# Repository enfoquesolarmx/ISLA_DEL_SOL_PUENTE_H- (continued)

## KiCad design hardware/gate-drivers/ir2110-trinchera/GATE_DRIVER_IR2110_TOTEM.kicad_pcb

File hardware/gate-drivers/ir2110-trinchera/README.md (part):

# Módulo gate driver de medio puente H con IR2110 + tótem TIP41C/TIP42C — modo trinchera

**Proyecto:** Puente H — prototipo SPWM "Isla del Sol" (inversor 48 V → 127 V / 60 Hz, 1000 W; modo cargador 1 kVA)
**Módulo:** gate driver de **medio puente H** (una rama: MOSFET alto + MOSFET bajo), legacy / trinchera, con tótem por canal
**Intercambiable con:** IRS2186, UCC21520DW y TLP250 de trinchera (misma interfaz J2/J5, mismo firmware)
**Versión de placa:** V.0.1.NOV.26.J.G
**Estado:** diseño terminado; DRC con 0 errores y 0 elementos sin conectar; esquemático por bloques con guía de trinchera (2026-11-12). Pendiente: fabricación y validación en banco
**Fecha:** 2026-11-04 (esquemático por bloques: 2026-11-12)
**Documentos relacionados:** [`docs/identificacion_dt_pin9.md`](../../../docs/identificacion_dt_pin9.md), [`docs/sensado_corriente.md`](../../../docs/sensado_corriente.md), [módulo TLP250](../tlp250-trinchera/README.md), [módulo IRS2186](../irs2186/README.md)

| Cara de componentes | Cara de soldadura |
| --- | --- |
|  |  |

*Izquierda: arriba, la bornera J2 de entrada con R1 y R2 (10 kΩ, pull-down de HIN y LIN); en medio, el **IR2110 en DIP-14** con sus capacitores X7R; abajo, los **cuatro TO-220 del tótem** (TIP41C o D44H11 como NPN, TIP42C o D45H11 como PNP) y el header J5 hacia el puente H (H · VS1 · · · GK · L · G · 15V · llave · NC). La leyenda **"USAR SILICÓN RTV NEUTRO ENTRE TIPs"** recuerda fijar los transistores a la tarjeta con silicón de curado neutro. Derecha: la leyenda **"ATENCIÓN: DT = 1 µs — VALIDAR MOSFET Y SW"**, el regulador **78L05** (SOT-89) que da los 5 V de VDD, la red de bootstrap (2.2 Ω 1 W + ES1D), los dos **zener de 18 V** (Z1: VB1–VS1 y Z2: 15V–GND_K) y la **X** de la llave en la posición 8 de J5.*

*Esquemático por bloques (KiCad 9, hoja A3), pensado para quien arma y repara: **A** entrada J2 · **B** lógica de 5 V con 78L05 · **C** IR2110 · **D** 15 V del lado bajo · **E** bootstrap · **F** tótem alto · **G** tótem bajo · **H** salida J5 · **I** guía rápida de trinchera (ensamble y prueba sin MOSFET). Cada bloque dice qué medir y qué pasa si una pieza va al revés.*

## 0. Guía rápida de trinchera

**Antes de soldar:**

| Pieza | Cuidado | Si se hace mal |
| --- | --- | --- |
| U1 IR2110 | En **zócalo DIP-14**, muesca hacia el pin 1 | Se cambia sin cautín; al revés se quema al conectar |
| J5 | **Quitar el pin 8** del header (llave) | El módulo podría entrar al revés en el puente H |
| Z1 | Banda (cátodo) hacia **VB1** | Pone en corto el bootstrap: el MOSFET alto nunca enciende |
| Z2 | Banda (cátodo) hacia **15 V** | Se calienta y jala los 15 V |
| Q1–Q4 | NPN (TIP41C / D44H11G) arriba, PNP (TIP42C / D45H11G) abajo; acostados, aletas sin tocarse | NPN y PNP cruzados: la salida no sigue a la entrada |
| TIPs | Silicón RTV **neutro** entre los cuerpos y el PCB | El silicón acético corroe las patas |

**Prueba sin MOSFET** (15 V en J5-7; J5-6 y J5-4 a la tierra de la fuente; **J5-2 (VS1) unido a J5-4** para que cargue el bootstrap; J2 a la tarjeta de control o a 5 V):

| Medir | Entre | Debe dar |
| --- | --- | --- |
| VDD | Pin 9 y pin 13 del IR2110 | 5.0 V ± 0.25 V |
| VCC | Pin 3 y pin 2 | 15 V |
| SD | Pin 11 a GND | 0 V |
| Salidas con J2 suelto | HA_OUT (J5-1) y LA_OUT (J5-5) | 0 V |
| L = 5 V | LA_OUT a GND_K | ≈ 14 V (15 V menos el V_BE del tótem) |
| H = 5 V (después de un pulso de L, para cargar el bootstrap) | HA_OUT a VS1 | ≈ 13 V |
| Tiempo muerto | Lo que reporta el MCU | **1 µs** (P9 abierto) |

> Valores verificados contra `GATE_DRIVER_IR2110_TOTEM.kicad_pcb` (2026-11-04). Lo marcado *(verificar)* depende de la hoja de datos.

---
## 1. Qué maneja este módulo

Cada módulo maneja **una rama** del puente H: el **MOSFET del lado alto** (HO, referido a VS, alimentado por bootstrap) y el **MOSFET del lado bajo** (LO, referido a COM / GND_K).

```
            +48 V
              │
     HA ──► [MOSFET alto]          [MOSFET alto] ◄── HB
              │                         │
              ├── VS1 ──► transformador ◄── VS2 ──┤
              │                         │
     LA ──► [MOSFET bajo]          [MOSFET bajo] ◄── LB
              │                         │
             GND ───────────────────── GND
         └── módulo rama A ──┘    └── módulo rama B ──┘
```

- **El puente completo usa dos módulos iguales:** rama A (VS1) y rama B (VS2). En la rama B, "H" y "L" de J2 manejan HB y LB, y el pin "VS1" de J5 va a VS2.
- **Inversor (modulación híbrida):** rama A a **24 kHz**, rama B a **60 Hz**. **Cargador (unipolar):** las dos ramas a **24 kHz**.
- **Alcance: de 1 a 5 MOSFET por posición** (sección 6).

### 1.1 Por qué existe: modo trinchera

Igual que el módulo TLP250, este módulo existe para **cuando los drivers modernos no llegan**. El IR2110 (International Rectifier, hoy Infineon) es el driver de medio puente **más fácil de conseguir o rescatar**: está en variadores, soldadoras inverter y UPS viejos, y en casi cualquier tienda de electrónica. Viene en **DIP-14**: se monta en zócalo y se cambia sin cautín. Todo el módulo se arma con partes de tienda local.

| | TLP250 + tótem | **IR2110 + tótem (este)** |
| --- | --- | --- |
| Driver | Optoacoplador DIP-8, uno por canal | DIP-14, un chip para los dos canales |
| Aislamiento de la entrada | Sí (óptico) | Parcial: **VSS y COM separados**, hasta ±5 V |
| Diferencia de retardo entre canales | Hasta **400 ns** | **10–20 ns** |
| Margen dentro de 1 µs | ~150–250 ns con 2 IRF100P219 | **Mucho mayor** |
| Corriente propia | ~2 A | 2 A |
| MOSFET por posición | 1–2 IRF100P219 | **1–5** (por ejemplo 5 × IRF540N) |

---

## 2. Interfaz

### 2.1 J2 — entrada, hacia la tarjeta de control ("J1" de la interfaz)

Conector **Phoenix Contact SPT 1,5/5-H-3,5** (5 posiciones, paso 3.5 mm, de resorte), igual que el módulo IRS2186.

| Terminal | Señal | En este módulo |
| --- | --- | --- |
| 1 | H | HIN del IR2110 (pin 10), 10 kΩ a GND |
| 2 | GND | Tierra lógica = VSS (trenzar con H) |
| 3 | L | LIN del IR2110 (pin 12), 10 kΩ a GND |
| 4 | GND | Tierra lógica = VSS (trenzar con L) |
| **5** | **P9 — ID DT** | **Abierto, sin pista** → el MCU usa **1 µs** |

### 2.2 J5 — salida, hacia la tarjeta del puente H (header de 9 posiciones, 2.54 mm)

| Pin | Señal | Nota |
| --- | --- | --- |
| 1 | H (HA_OUT) | Emisores del tótem H |
| 2 | VS1 | Referencia del canal H |
| 3 | — | Libre (separación del nodo conmutado) |
| 4 | GK (GND_K) | Referencia Kelvin del canal L = **COM** |
| 5 | L (LA_OUT) | Emisores del tótem L |
| 6 | G (GND) | **Tierra lógica (VSS)**: retorno del 78L05 hacia la tarjeta del puente H |
| 7 | 15 V | Alimentación |
| 8 | **X** | **Llave mecánica:** sin pad; **quitar el pin 8 del header** |
| 9 | NC | Reservado |

### 2.3 Tierras: VSS y COM separados

El IR2110 tiene **dos tierras**: **VSS** (lógica) y **COM** (retorno del lado bajo), con hasta **±5 V** de diferencia permitida.

| Zona | Referencia | Componentes |
| --- | --- | --- |
| Lógica | **GND (VSS)** | J2, R1, R2, VSS (13), SD (11), 78L05, capacitor de entrada y de salida del 78L05, **J5-6** |
| Canal L (potencia) | **GND_K (COM)** | COM (2), colector de Q4 (PNP), C2, C4, C6, C8, Z2 |
| Canal H (HV, flota con VS1) | **VS1** | VS (5), Q2 colector, C3, C5, C9, Z1 |

- **J5-6 a GND lógico** (a diferencia del TLP250, que deja J5-6 sin conectar): el 78L05 toma sus 15 V de J5-7, así que su corriente regresa por el camino corto J5-6. Además, VSS queda bien referido respecto a COM.
- **COM va a GND_K (J5-4):** la corriente de compuerta del canal bajo regresa por GND_K y **no pasa por la tierra lógica**. Es la ventaja del IR2110 sobre el IRS2186.
- GND y GND_K se unen en **un solo punto en la tarjeta del puente H**, nunca dentro del módulo.
- **Lazo de tierra:** igual que con el IRS2186, el GND del cable J2 es un camino más hacia la tarjeta de control. Se controla con **par trenzado H/GND y L/GND** y la unión única de tierras.
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
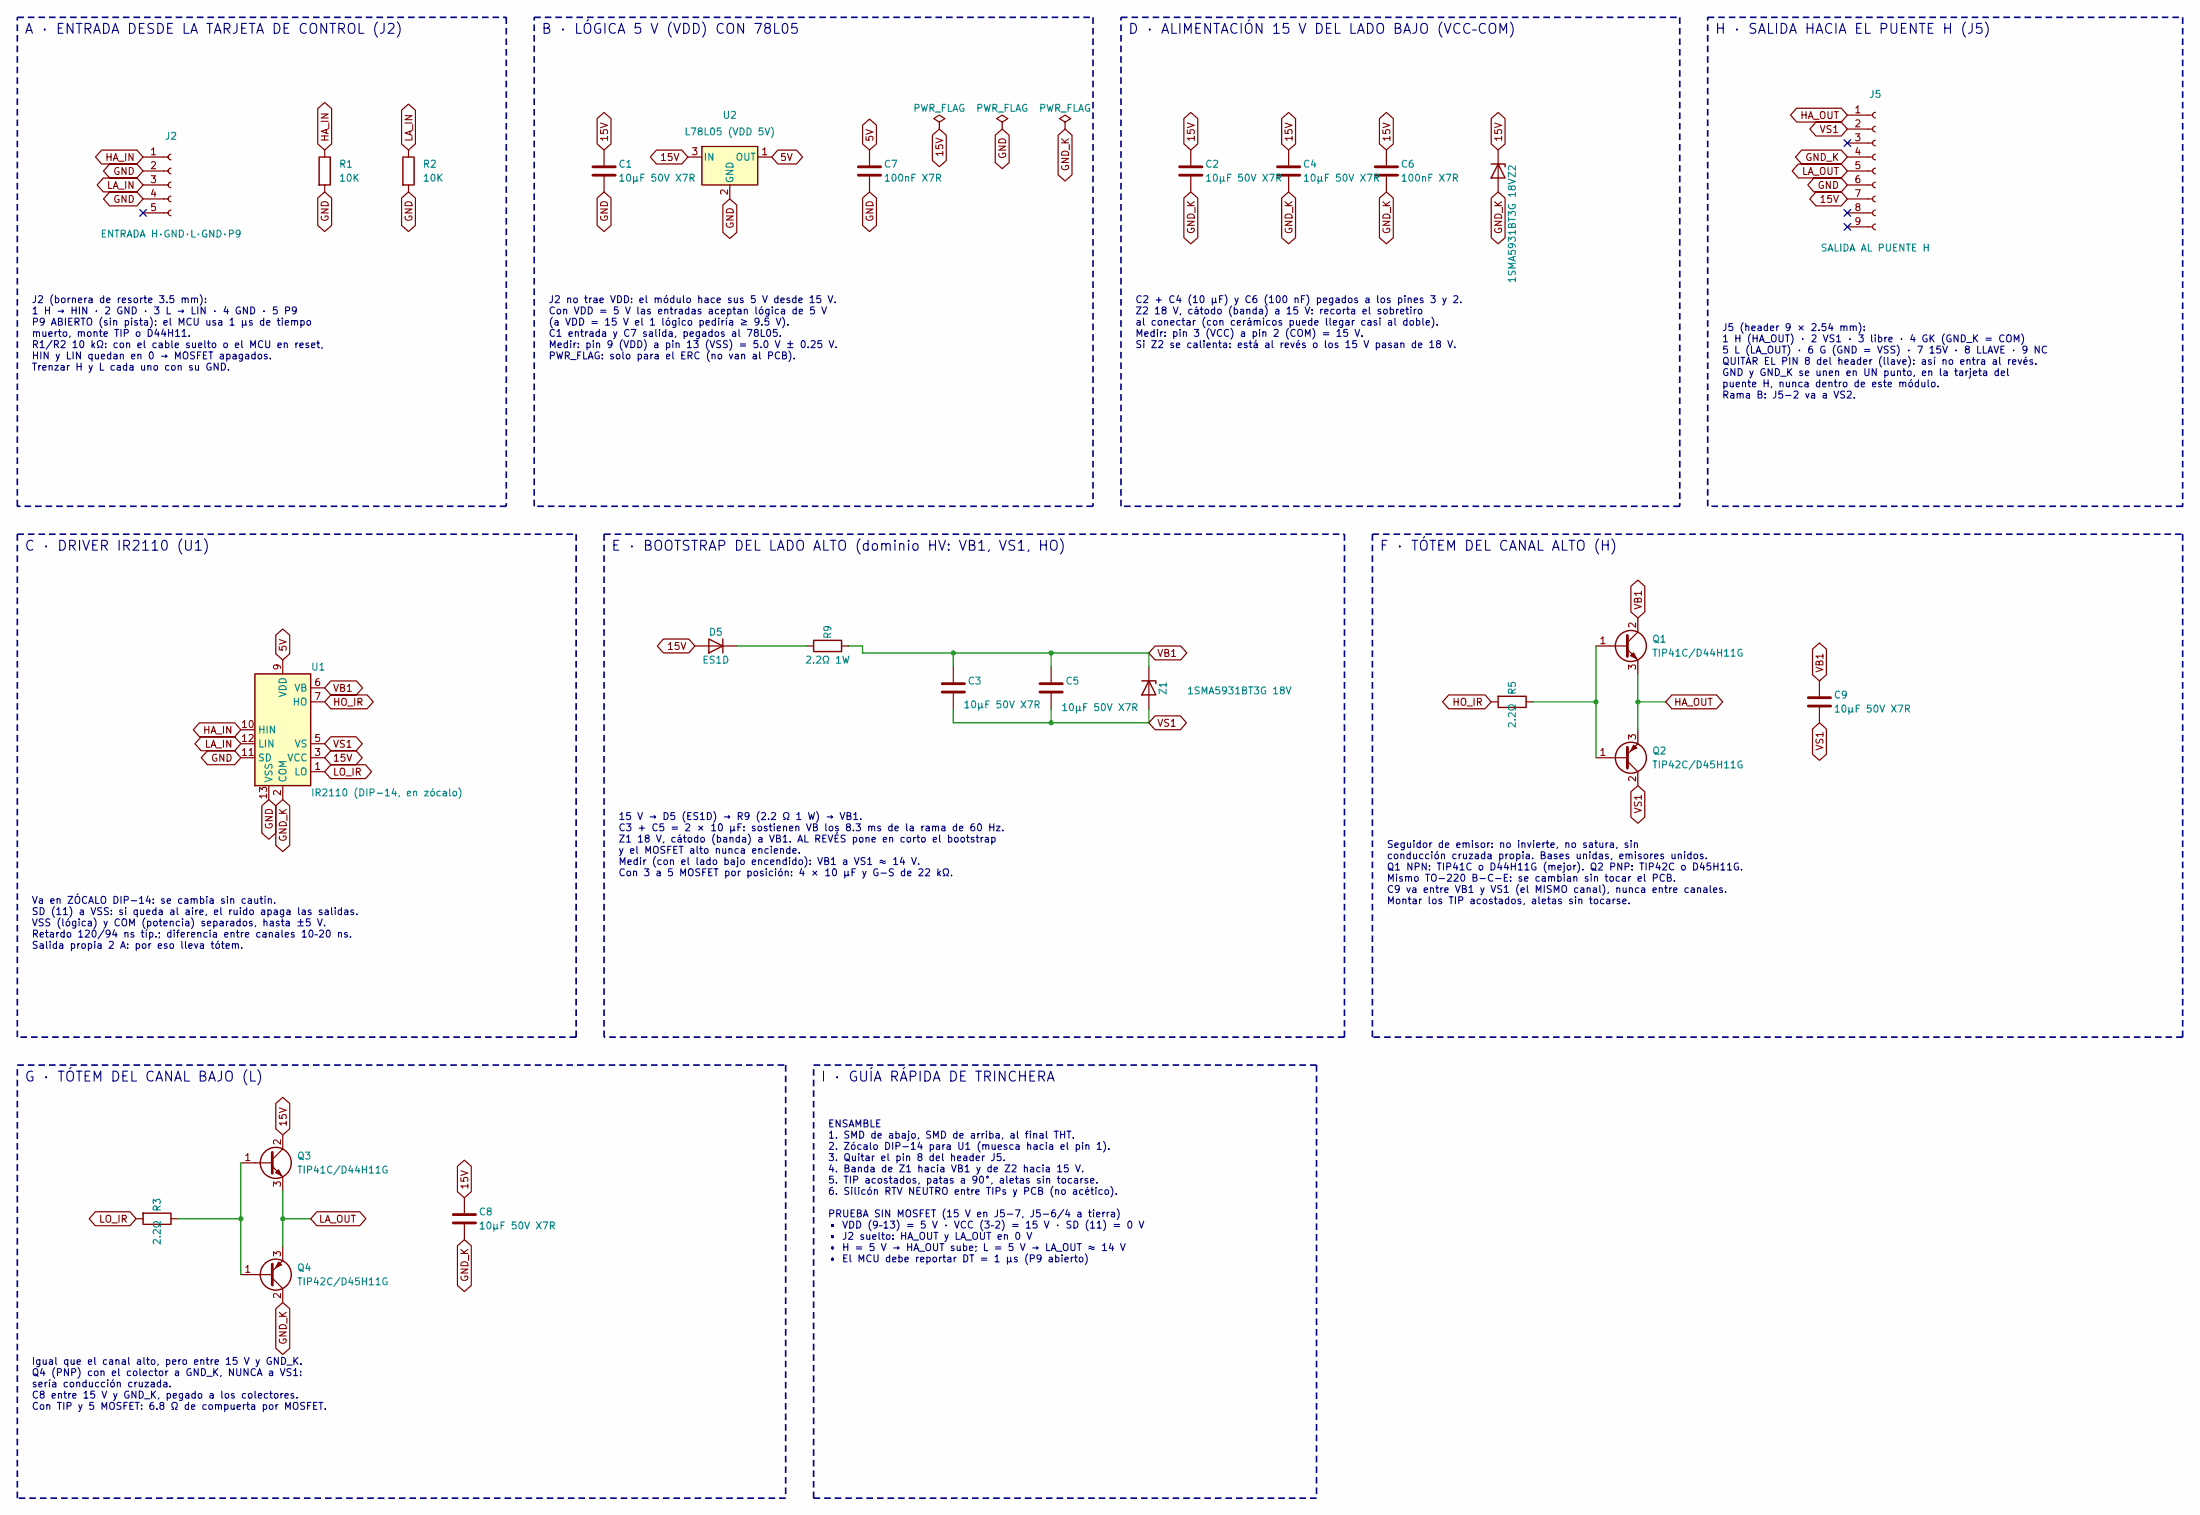
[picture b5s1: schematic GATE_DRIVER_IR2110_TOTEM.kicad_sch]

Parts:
C1, C2, C3, C4, C5, C8, C9: 10µF 50V X7R; C_1210_3225Metric_Pad1.33x2.70mm_HandSolder
C6, C7: 100nF X7R; C_1206_3216Metric
D5: ES1D; D_SMA
J2: ENTRADA H·GND·L·GND·P9; PhoenixContact_SPT_1.5_5-H-3.5_1x05_P3.5mm_Horizontal
J5: SALIDA AL PUENTE H; PinHeader_1x09_P2.54mm_Vertical
Q1, Q3: TIP41C/D44H11G; TO-220-3_Vertical
Q2, Q4: TIP42C/D45H11G; TO-220-3_Vertical
R1, R2: 10K; R_1206_3216Metric_Pad1.30x1.75mm_HandSolder
R3, R5: 2.2Ω; R_1206_3216Metric_Pad1.30x1.75mm_HandSolder
R9: 2.2Ω 1W; R_1210_3225Metric
U1: IR2110 (DIP-14, en zócalo); DIP-14_W7.62mm
U2: L78L05 (VDD 5V); SOT-89-3
Z1, Z2: 1SMA5931BT3G 18V; D_SMA

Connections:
5V: C7.1, U1.9 (VDD), U2.1 (OUT)
15V: C1.1, C2.1, C4.1, C6.1, C8.1, D5.2 (A), J5.7, Q3.2 (C), U1.3 (VCC), U2.3 (IN), Z2.1 (K)
GND: C1.2, C7.2, J2.2, J2.4, J5.6, R1.2, R2.2, U1.11 (SD), U1.13 (VSS), U2.2 (GND)
GND_K: C2.2, C4.2, C6.2, C8.2, J5.4, Q4.2 (C), U1.2 (COM), Z2.2 (A)
HA_IN: J2.1, R1.1, U1.10 (HIN)
HA_OUT: J5.1, Q1.3 (E), Q2.3 (E)
HO_IR: R5.2, U1.7 (HO)
LA_IN: J2.3, R2.1, U1.12 (LIN)
LA_OUT: J5.5, Q3.3 (E), Q4.3 (E)
LO_IR: R3.2, U1.1 (LO)
unnamed: D5.1 (K), R9.2
unnamed: Q1.1 (B), Q2.1 (B), R5.1
unnamed: Q3.1 (B), Q4.1 (B), R3.1
VB1: C3.1, C5.1, C9.1, Q1.2 (C), R9.1, U1.6 (VB), Z1.1 (K)
VS1: C3.2, C5.2, C9.2, J5.2, Q2.2 (C), U1.5 (VS), Z1.2 (A)

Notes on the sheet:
H · SALIDA HACIA EL PUENTE H (J5)
ENSAMBLE 1. SMD de abajo, SMD de arriba, al final THT. 2. Zócalo DIP-14 para U1 (muesca hacia el pin 1). 3. Quitar el pin 8 del header J5. 4. Banda de Z1 hacia VB1 y de Z2 hacia 15 V. 5. TIP acostados, patas a 90°, aletas sin tocarse. 6. Silicón RTV NEUTRO entre TIPs y PCB (no acético). PRUEBA SIN 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
I · GUÍA RÁPIDA DE TRINCHERA
C2 + C4 (10 µF) y C6 (100 nF) pegados a los pines 3 y 2. Z2 18 V, cátodo (banda) a 15 V: recorta el sobretiro al conectar (con cerámicos puede llegar casi al doble). Medir: pin 3 (VCC) a pin 2 (COM) = 15 V. Si Z2 se calienta: está al revés o los 15 V pasan de 18 V.
E · BOOTSTRAP DEL LADO ALTO (dominio HV: VB1, VS1, HO)
A · ENTRADA DESDE LA TARJETA DE CONTROL (J2)
F · TÓTEM DEL CANAL ALTO (H)
Seguidor de emisor: no invierte, no satura, sin conducción cruzada propia. Bases unidas, emisores unidos. Q1 NPN: TIP41C o D44H11G (mejor). Q2 PNP: TIP42C o D45H11G. Mismo TO-220 B-C-E: se cambian sin tocar el PCB. C9 va entre VB1 y VS1 (el MISMO canal), nunca entre canales. Montar los TIP acostado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
B · LÓGICA 5 V (VDD) CON 78L05
Igual que el canal alto, pero entre 15 V y GND_K. Q4 (PNP) con el colector a GND_K, NUNCA a VS1: sería conducción cruzada. C8 entre 15 V y GND_K, pegado a los colectores. Con TIP y 5 MOSFET: 6.8 Ω de compuerta por MOSFET.
D · ALIMENTACIÓN 15 V DEL LADO BAJO (VCC–COM)
Va en ZÓCALO DIP-14: se cambia sin cautín. SD (11) a VSS: si queda al aire, el ruido apaga las salidas. VSS (lógica) y COM (potencia) separados, hasta ±5 V. Retardo 120/94 ns típ.; diferencia entre canales 10–20 ns. Salida propia 2 A: por eso lleva tótem.
G · TÓTEM DEL CANAL BAJO (L)
C · DRIVER IR2110 (U1)
15 V → D5 (ES1D) → R9 (2.2 Ω 1 W) → VB1. C3 + C5 = 2 × 10 µF: sostienen VB los 8.3 ms de la rama de 60 Hz. Z1 18 V, cátodo (banda) a VB1. AL REVÉS pone en corto el bootstrap y el MOSFET alto nunca enciende. Medir (con el lado bajo encendido): VB1 a VS1 ≈ 14 V. Con 3 a 5 MOSFET por posición: 4 × 10 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
J5 (header 9 × 2.54 mm): 1 H (HA_OUT) · 2 VS1 · 3 libre · 4 GK (GND_K = COM) 5 L (LA_OUT) · 6 G (GND = VSS) · 7 15V · 8 LLAVE · 9 NC QUITAR EL PIN 8 del header (llave): así no entra al revés. GND y GND_K se unen en UN punto, en la tarjeta del puente H, nunca dentro de este módulo. Rama B: J5-2 va a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
J2 (bornera de resorte 3.5 mm): 1 H → HIN · 2 GND · 3 L → LIN · 4 GND · 5 P9 P9 ABIERTO (sin pista): el MCU usa 1 µs de tiempo muerto, monte TIP o D44H11. R1/R2 10 kΩ: con el cable suelto o el MCU en reset, HIN y LIN quedan en 0 → MOSFET apagados. Trenzar H y L cada uno con su GND.
J2 no trae VDD: el módulo hace sus 5 V desde 15 V. Con VDD = 5 V las entradas aceptan lógica de 5 V (a VDD = 15 V el 1 lógico pediría ≥ 9.5 V). C1 entrada y C7 salida, pegados al 78L05. Medir: pin 9 (VDD) a pin 13 (VSS) = 5.0 V ± 0.25 V. PWR_FLAG: solo para el ERC (no van al PCB).

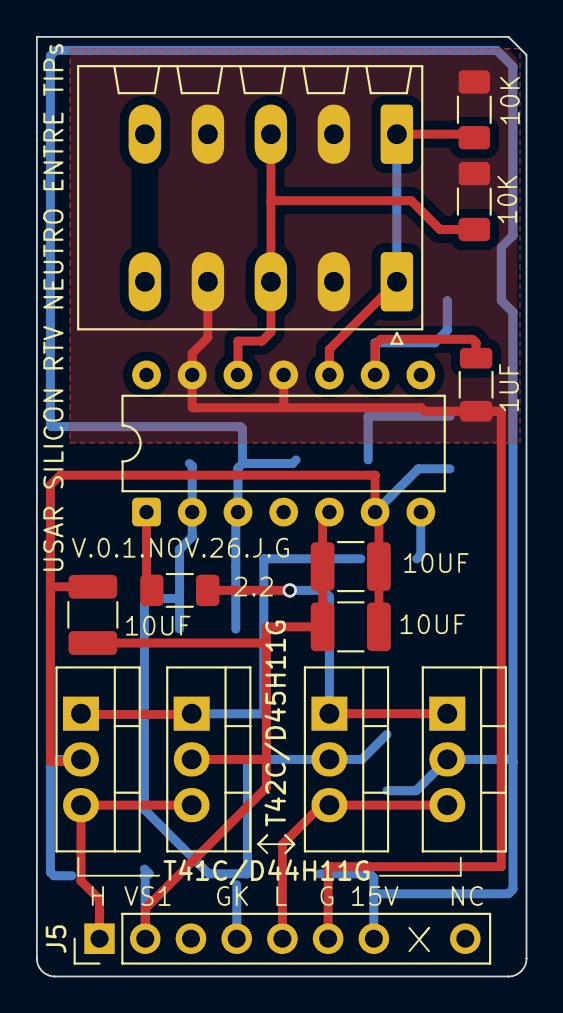
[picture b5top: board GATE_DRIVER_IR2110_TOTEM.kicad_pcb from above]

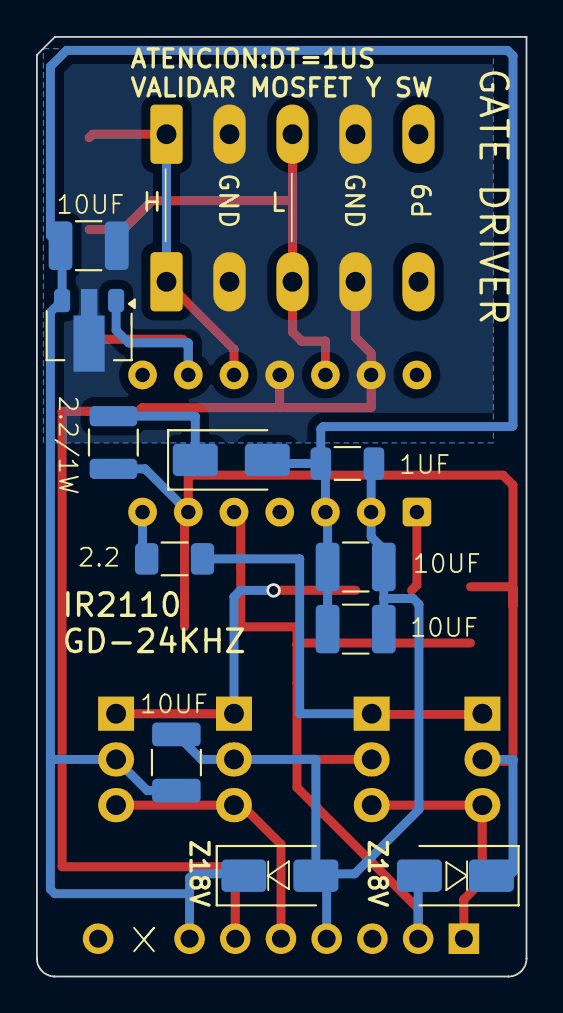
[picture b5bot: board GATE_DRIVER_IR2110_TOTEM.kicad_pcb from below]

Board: 2 copper layers, 27.2 x 52.2 mm, 25 parts (11 on the bottom side), 15 nets.

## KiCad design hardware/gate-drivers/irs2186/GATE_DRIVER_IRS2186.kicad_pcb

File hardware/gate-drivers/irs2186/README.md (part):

# Módulo gate driver de medio puente H con IRS2186

**Proyecto:** Puente H — prototipo SPWM "Isla del Sol" (inversor 48 V → 127 V / 60 Hz, 1000 W; modo cargador 1 kVA)
**Módulo:** gate driver de **medio puente H** (una rama: MOSFET alto + MOSFET bajo) con bootstrap. Es el **módulo principal de producción**: bajo costo y 500 ns de tiempo muerto
**Intercambiable con:** UCC21520DW y TLP250 de trinchera (misma interfaz J1/J5, mismo firmware)
**Estado:** diseño terminado con P9 en J1; esquemático reordenado por bloques (2026-11-12). Pendiente: DRC final, fabricación y validación en banco
**Fecha:** 2026-11-03 (esquemático por bloques: 2026-11-12)
**Documentos relacionados:** [`docs/identificacion_dt_pin9.md`](../../../docs/identificacion_dt_pin9.md), [`docs/compensacion_adaptativa_tiempo_muerto.md`](../../../docs/compensacion_adaptativa_tiempo_muerto.md), [módulo TLP250](../tlp250-trinchera/README.md)

> Verificar los valores marcados con *(verificar)* contra el esquemático de KiCad antes de fabricar.

| Cara de componentes | Cara de soldadura |
| --- | --- |
|  |  |

*Esquemático por bloques (KiCad 9, hoja A4): **A** entrada J1 con R1/R2 y P9 · **B** alimentación de 15 V · **C** IRS2186 · **D** bootstrap · **E** salida J5 y NT1 · **F** reglas de firmware y compras. Cada bloque lleva su nota de diseño.*

*Izquierda: arriba, la bornera J1 de entrada (**P**9 · GND · L · GND · H); en medio, el IRS2186 (SOIC-8) con su desacoplo de 15 V (1 µF + 10 µF), la red de bootstrap (2.2 Ω 1 W + ES1D), el zener D6 de 18 V (1SMA5931BT3G), los capacitores de bootstrap (2 × 10 µF) y el electrolítico de respaldo de 15 V; abajo, el header J5 hacia el puente H (HO · VS1 · · · Gk · LO · G · 15V · llave). Derecha: la leyenda de seguridad **"ATENCIÓN: DT 500 ns MIN — VALIDAR MOSFET Y SW"**, la versión V.0.1.NOV.26.J.G y la **X** de la llave en la posición 8 de J5.*

---

## 1. Qué maneja este módulo

Cada módulo maneja **una rama** del puente H: el **MOSFET del lado alto** (HO, referido a VS, alimentado por bootstrap) y el **MOSFET del lado bajo** (LO, referido a COM).

```
            +48 V
              │
     HA ──► [MOSFET alto]          [MOSFET alto] ◄── HB
              │                         │
              ├── VS1 ──► transformador ◄── VS2 ──┤
              │                         │
     LA ──► [MOSFET bajo]          [MOSFET bajo] ◄── LB
              │                         │
             GND ───────────────────── GND
         └── módulo rama A ──┘    └── módulo rama B ──┘
```

- **El puente completo usa dos módulos iguales:** rama A (VS1) y rama B (VS2). En la rama B, "H" y "L" de J1 manejan HB y LB, y el pin "VS1" de J5 va a VS2.
- **Inversor (modulación híbrida):** rama A a **24 kHz**, rama B a **60 Hz**.
- **Cargador (unipolar):** las dos ramas a **24 kHz**.
- **Alcance:** **1 IRF100P219 por posición** (o hasta 2 IRF540N) con 500 ns. Para más carga de compuerta hace falta tótem rápido o el módulo UCC21520 (ver sección 6).

### Por qué el IRS2186

| Criterio | IRS2186 (este) | UCC21520DW | TLP250 + tótem |
| --- | --- | --- | --- |
| Costo y número de componentes | **El menor** ✓ | Medio | El mayor |
| Tiempo muerto | **500 ns** ✓ | 500 ns | 1 µs |
| Corriente de salida | 4 A / 4 A | 4 A / 6 A | ~2 A (más con tótem) |
| Aislamiento entrada / potencia | **No** (lógica referida a COM) | Sí | Sí |
| Reparación a mano | SOIC-8 | SOIC-16 ancho | DIP y TO-220 |

---

## 2. Interfaz

### 2.1 J1 — entrada, hacia la tarjeta de control (bornera de 5 terminales)

| Terminal | Señal | En este módulo |
| --- | --- | --- |
| 1 | H | HIN del IRS2186 (con 10 kΩ a GND) |
| 2 | GND | Tierra lógica = COM (trenzar con H) |
| 3 | L | LIN del IRS2186 (con 10 kΩ a GND) |
| 4 | GND | Tierra lógica = COM (trenzar con L) |
| **5** | **P9 — ID DT** | **Unido a GND** → el MCU usa **500 ns** |

- Serigrafía: "TRENZAR H Y L CON GND", etiquetas H / GND / L / GND / P9. Recomendado agregar **"OPERACION DT IRS2186=500NS"**.
- Las resistencias de 10 kΩ de HIN y LIN a GND mantienen los MOSFET apagados si la tarjeta de control no está conectada o el MCU está en reset.
- Si P9 queda con soldadura fría o cable suelto, el MCU lee 1 → **1 µs** (falla segura: funciona con más armónicos).

### 2.2 J5 — salida, hacia la tarjeta del puente H (header de 9 posiciones, 2.54 mm)

| Pin | Señal | Nota |
| --- | --- | --- |
| 1 | HO | Compuerta lado alto |
| 2 | VS1 | Fuente lado alto (nodo de conmutación) |
| 3 | — | Libre (separación del nodo conmutado) |
| 4 | GND_K | Retorno Kelvin del lado bajo |
| 5 | LO | Compuerta lado bajo |
| 6 | GND | Tierra de potencia |
| 7 | 15 V | Alimentación |
| 8 | — | **Llave mecánica:** sin pad; **quitar el pin 8 del header**; "X" en serigrafía |
| 9 | GND | Reservado (no se lee) |

### 2.3 Tierras: la entrada comparte la tierra de potencia

En el IRS2186 la lógica (HIN, LIN) va referida a **COM**, que también es el retorno del lado bajo. Por eso **el GND de J1 es la misma tierra de potencia**: el módulo no aísla la tarjeta de control.

Consecuencias y cuidados:

1. **Lazo de tierra:** el GND del cable J1 es un camino más entre la tarjeta de control y la potencia; con dos módulos (rama A y B) ya hay dos. Parte de la corriente de conmutación puede circular por esos cables.
2. **Rebote de tierra:** el di/dt del MOSFET bajo puede mover COM unos cientos de mV respecto al GND del MCU. El IRS2186 tiene umbrales de entrada de ~0.8 V / ~2.5 V *(verificar en la hoja de datos)*; con MCU a 5 V el margen es mayor.
3. **Medidas:**
   - **Par trenzado H/GND y L/GND, lo más corto posible.**
   - **Un solo punto de unión** entre tierra de control y tierra de potencia en la tarjeta del puente H (estrella), cerca de la fuente del MOSFET bajo o del shunt.
   - **Retorno de LO hacia GND_K** (Kelvin) y lógica hacia GND, unidos en un solo punto: la corriente de compuerta no debe pasar por la tierra de las entradas.
4. Si en banco aparecen disparos falsos o ruido en las entradas, los módulos **UCC21520** o **TLP250** lo eliminan por diseño (entrada aislada).

---

## 3. Circuito

### 3.1 IRS2186 (SOIC-8)

| Pin | Señal | Conexión |
| --- | --- | --- |
| 1 | HIN | J1-H, 10 kΩ a GND |
| 2 | LIN | J1-L, 10 kΩ a GND |
| 3 | COM | GND (tierra lógica y retorno del lado bajo) |
| 4 | LO | J5-5 |
| 5 | VCC | 15 V, con desacoplo a COM |
| 6 | VS | J5-2 (VS1) |
| 7 | HO | J5-1 |
| 8 | VB | VB1, nodo del bootstrap |

Verificar contra la hoja de datos de la variante comprada (IRS2186S, SOIC-8).

**Datos de la hoja de datos (Infineon IRS2186):** salida 4 A / 4 A; retardo de propagación ~170 ns típ., 250 ns máx.; diferencia entre canales ≤ 35 ns; VCC 10–20 V; offset VS hasta 600 V *(verificar)*.

### 3.2 Alimentación de 15 V (lado bajo)

- 15 V desde J5-7 a VCC, con desacoplo **10 µF + 1 µF X7R** pegados a los pines 5 y 3, más capacitor electrolítico de respaldo en la línea de 15 V *(verificar valores)*.
- **¿Por qué 15 V y no 12 V?** Más voltaje de compuerta (menor R_DS(on) y más margen de UVLO en el bootstrap de la rama de 60 Hz) dentro del rango de VCC del IRS2186 y del ±20 V de V_GS del MOSFET.

### 3.3 Bootstrap (lado alto)

```
15 V ── D5 (ES1D / ES1J) ── R9 2.2 Ω 1 W ──┬── VB1 (pin 8)
                                           ├── C2 + C9: 2 × 10 µF X7R 50 V 1206 ── VS1
                                           └── D6 zener 18 V (1SMA5931BT3G), cátodo a VB1 ── VS1
```

| Componente | Valor | Por qué |
| --- | --- | --- |
| R9 | 2.2 Ω, 1 W, **después del diodo** (entre el cátodo de D5 y VB1) | Limita el pico de recarga del bootstrap cuando VS cae a 0 V y, en esta posición, también la corriente de recuperación inversa de D5 cuando VS sube (IR Design Tip DT98-2; TI SLUA887A; patente US5969964, ya expirada). La resistencia en serie con el diodo cumple igual antes o después de él |
| D5 | ES1D (200 V) o **ES1J (600 V)** | Diodo **ultrarrápido** (no Schottky). ES1D limita el bus del módulo a ~120 V; con ES1J el límite lo ponen las separaciones del PCB (≤ 150 V) |
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
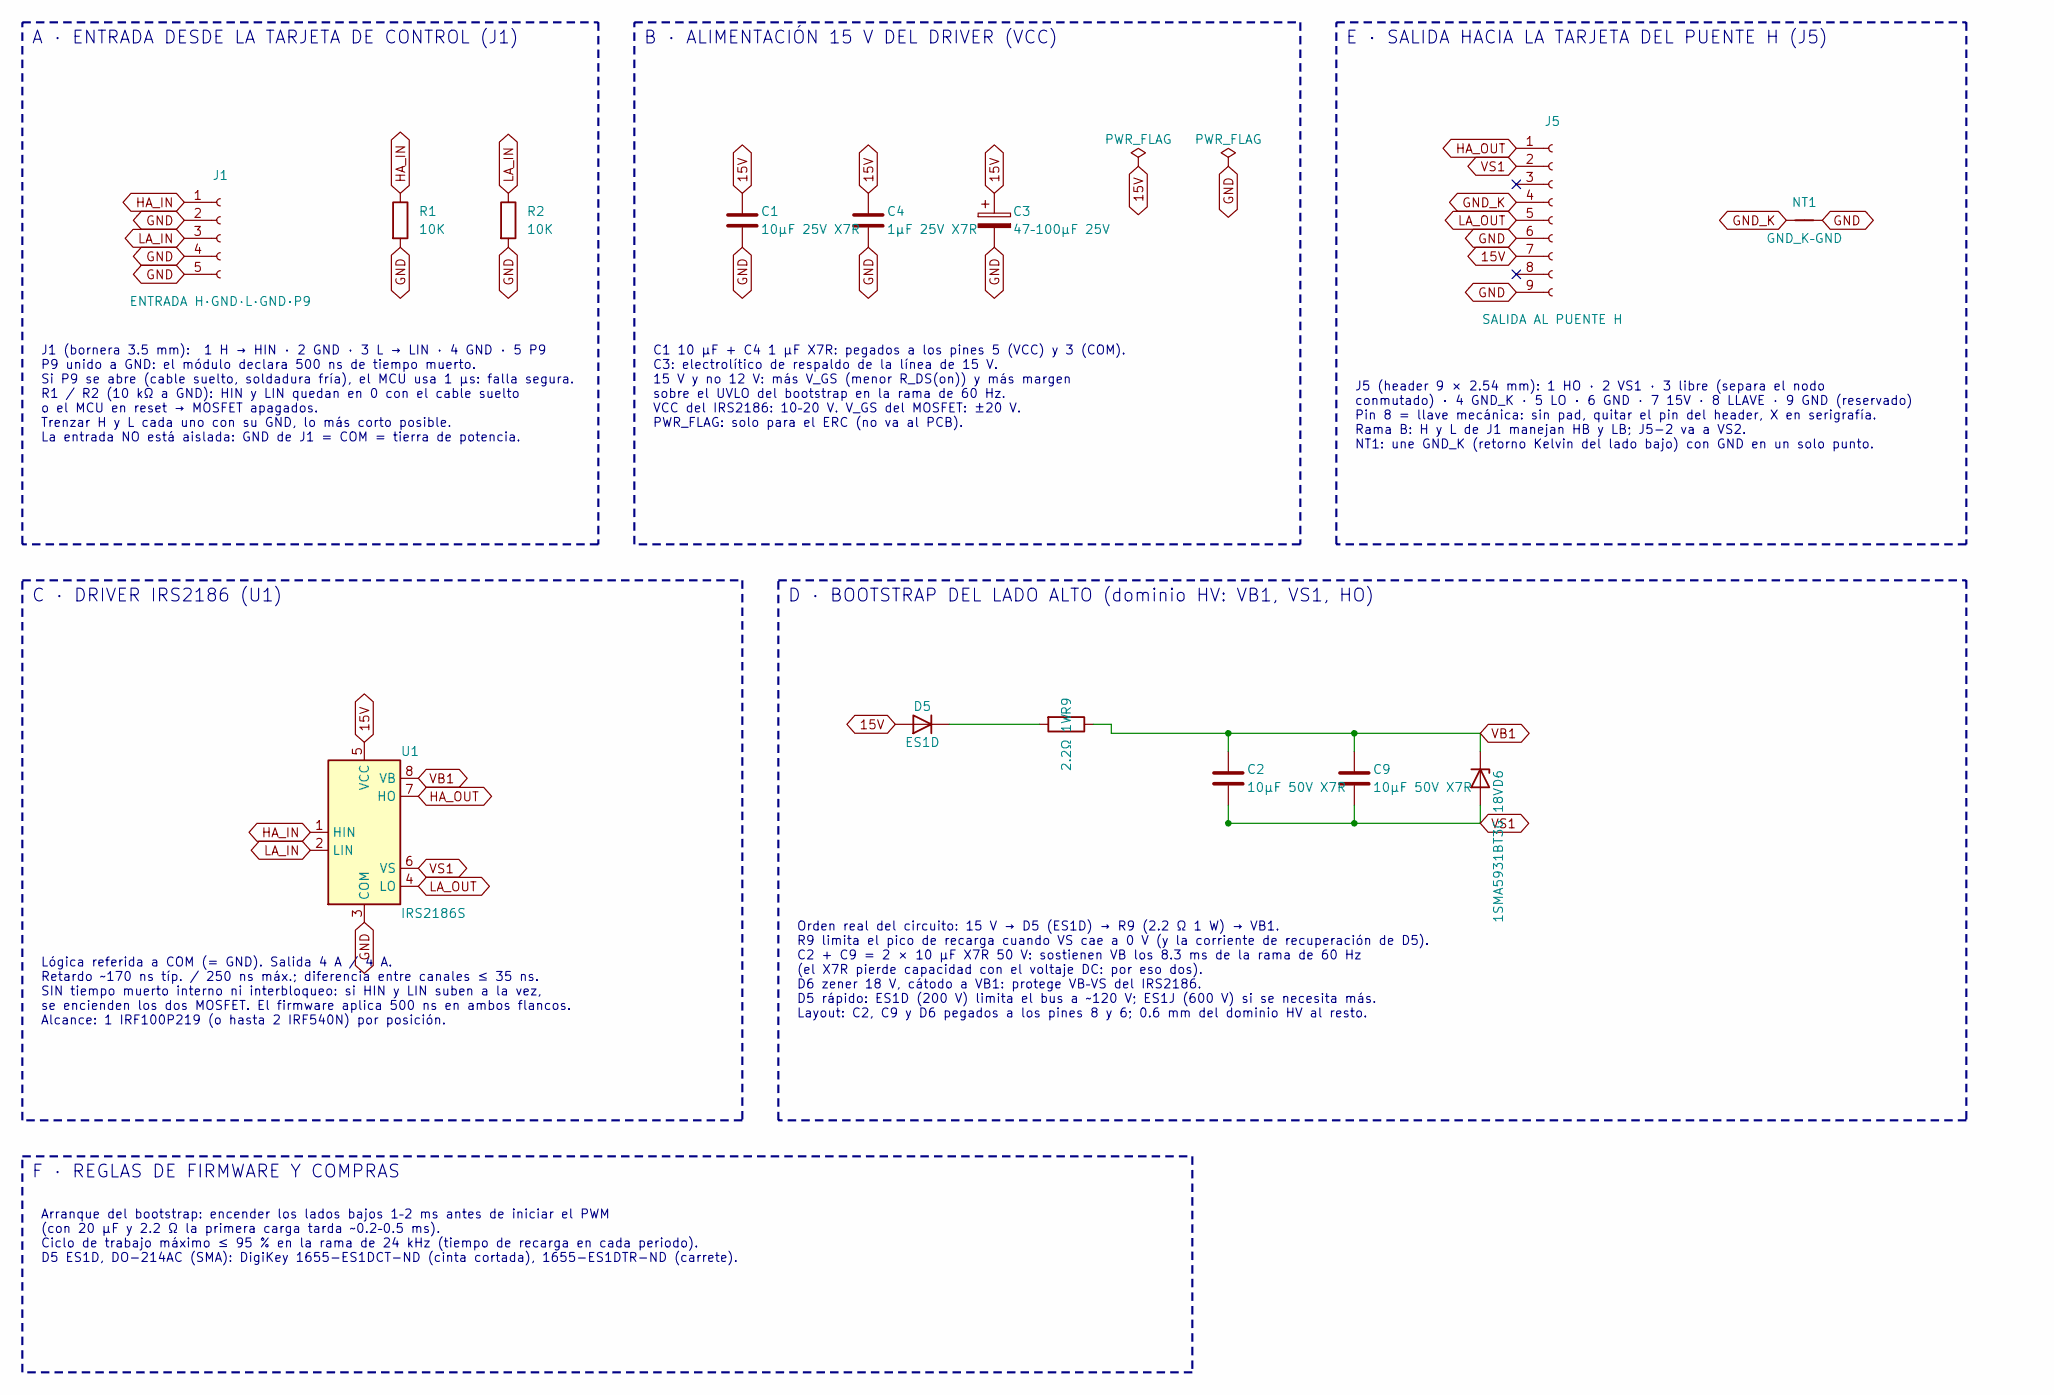
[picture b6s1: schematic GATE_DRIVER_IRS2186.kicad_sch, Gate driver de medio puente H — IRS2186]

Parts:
C1: 10µF 25V X7R; C_1206_3216Metric
C2, C9: 10µF 50V X7R; C_1206_3216Metric
C3: 47–100µF 25V; CP_Radial_D8.0mm_P3.50mm
C4: 1µF 25V X7R; C_1206_3216Metric
D5: ES1D; D_SMA
D6: 1SMA5931BT3G 18V; D_SMA
J1: ENTRADA H·GND·L·GND·P9; PhoenixContact_SPT_1.5_5-H-3.5_1x05_P3.5mm_Horizontal
J5: SALIDA AL PUENTE H; PinHeader_1x09_P2.54mm_Vertical
NT1: GND_K–GND; NetTie-2_SMD_Pad0.5mm
R1, R2: 10K; R_1206_3216Metric_Pad1.30x1.75mm_HandSolder
R9: 2.2Ω 1W; R_1210_3225Metric
U1: IRS2186S; SOIC-8_3.9x4.9mm_P1.27mm

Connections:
15V: C1.1, C3.1, C4.1, D5.2 (A), J5.7, U1.5 (VCC)
GND: C1.2, C3.2, C4.2, J1.2, J1.4, J1.5, J5.6, J5.9, NT1.2, R1.2, R2.2, U1.3 (COM)
GND_K: J5.4, NT1.1
HA_IN: J1.1, R1.1, U1.1 (HIN)
HA_OUT: J5.1, U1.7 (HO)
LA_IN: J1.3, R2.1, U1.2 (LIN)
LA_OUT: J5.5, U1.4 (LO)
unnamed: D5.1 (K), R9.2
VB1: C2.1, C9.1, D6.1 (K), R9.1, U1.8 (VB)
VS1: C2.2, C9.2, D6.2 (A), J5.2, U1.6 (VS)

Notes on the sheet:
A · ENTRADA DESDE LA TARJETA DE CONTROL (J1)
J1 (bornera 3.5 mm): 1 H → HIN · 2 GND · 3 L → LIN · 4 GND · 5 P9 P9 unido a GND: el módulo declara 500 ns de tiempo muerto. Si P9 se abre (cable suelto, soldadura fría), el MCU usa 1 µs: falla segura. R1 / R2 (10 kΩ a GND): HIN y LIN quedan en 0 con el cable suelto o el MCU en reset → MOSFET apaga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
B · ALIMENTACIÓN 15 V DEL DRIVER (VCC)
C1 10 µF + C4 1 µF X7R: pegados a los pines 5 (VCC) y 3 (COM). C3: electrolítico de respaldo de la línea de 15 V. 15 V y no 12 V: más V_GS (menor R_DS(on)) y más margen sobre el UVLO del bootstrap en la rama de 60 Hz. VCC del IRS2186: 10–20 V. V_GS del MOSFET: ±20 V. PWR_FLAG: solo para el ERC (no 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
E · SALIDA HACIA LA TARJETA DEL PUENTE H (J5)
J5 (header 9 × 2.54 mm): 1 HO · 2 VS1 · 3 libre (separa el nodo conmutado) · 4 GND_K · 5 LO · 6 GND · 7 15V · 8 LLAVE · 9 GND (reservado) Pin 8 = llave mecánica: sin pad, quitar el pin del header, X en serigrafía. Rama B: H y L de J1 manejan HB y LB; J5-2 va a VS2. NT1: une GND_K (retorno Kelvin de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
C · DRIVER IRS2186 (U1)
Lógica referida a COM (= GND). Salida 4 A / 4 A. Retardo ~170 ns típ. / 250 ns máx.; diferencia entre canales ≤ 35 ns. SIN tiempo muerto interno ni interbloqueo: si HIN y LIN suben a la vez, se encienden los dos MOSFET. El firmware aplica 500 ns en ambos flancos. Alcance: 1 IRF100P219 (o hasta 2 IR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
D · BOOTSTRAP DEL LADO ALTO (dominio HV: VB1, VS1, HO)
Orden real del circuito: 15 V → D5 (ES1D) → R9 (2.2 Ω 1 W) → VB1. R9 limita el pico de recarga cuando VS cae a 0 V (y la corriente de recuperación de D5). C2 + C9 = 2 × 10 µF X7R 50 V: sostienen VB los 8.3 ms de la rama de 60 Hz (el X7R pierde capacidad con el voltaje DC: por eso dos). D6 zener 18 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
F · REGLAS DE FIRMWARE Y COMPRAS
Arranque del bootstrap: encender los lados bajos 1–2 ms antes de iniciar el PWM (con 20 µF y 2.2 Ω la primera carga tarda ~0.2–0.5 ms). Ciclo de trabajo máximo ≤ 95 % en la rama de 24 kHz (tiempo de recarga en cada periodo). D5 ES1D, DO-214AC (SMA): DigiKey 1655-ES1DCT-ND (cinta cortada), 1655-ES1D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

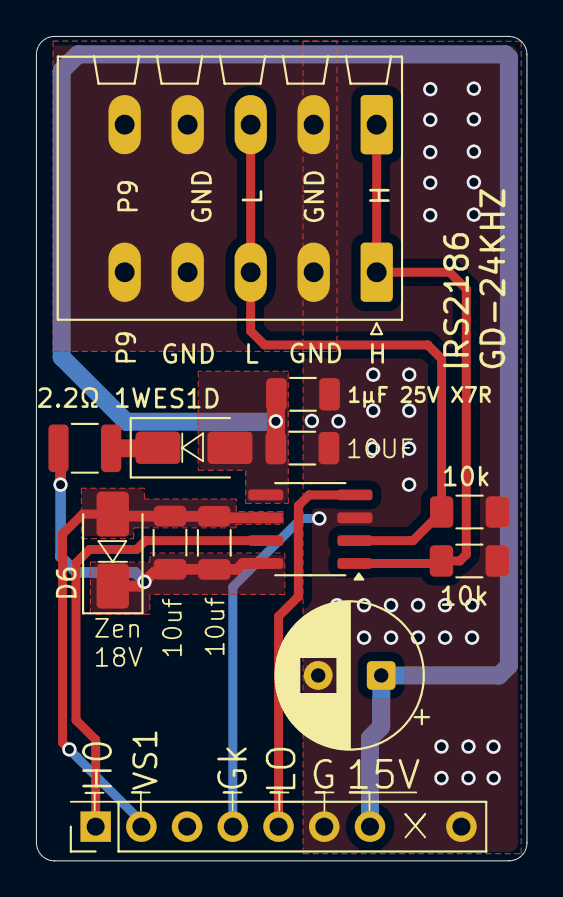
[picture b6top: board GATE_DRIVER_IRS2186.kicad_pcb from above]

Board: 2 copper layers, 27.2 x 45.8 mm, 14 parts (1 on the bottom side), 10 nets.

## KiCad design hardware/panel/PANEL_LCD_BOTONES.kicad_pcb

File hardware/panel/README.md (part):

# Panel frontal V0.2: pantalla LCD I2C y 4 botones

El panel frontal es **la cara del inversor**. Sirve para dos cosas:
- **ver todos los datos** que miden las tarjetas: red, salida, batería, potencia, temperatura, protecciones y estado de los relés;
- **configurar el inversor** desde el menú del **SETUP**, entre otras cosas el modo **INVERSOR CASA / INVERSOR CARGA (UPS)**, que decide la unión N–PE (DC-019).

Se conecta con un solo cable de 5 hilos a **J7 de la [tarjeta de control](../control/README.md)**. Lo maneja el microcontrolador **AUX**. El CRÍTICO mide y protege, y el AUX solo muestra y pide cambios. **Si el panel se desconecta o se cuelga, el inversor sigue funcionando y protegiendo igual.**

> **Para quien arma y repara en la trinchera:** igual que en las otras tarjetas, cada bloque dice **qué hace**, **por qué tiene ese valor** y **qué pasa si falla**. Antes de fabricar, revisa la sección [6. Verificar antes de fabricar](#6-verificar-antes-de-fabricar): la posición del zócalo del módulo I2C se mide con el módulo real.

*PCB V0.2 de 116 × 100 mm, 2 capas. Dorado = cobre de arriba (F.Cu), azul = cobre de abajo (B.Cu). Se ven las dos siluetas (LCD 20×4 por fuera y 16×2 por dentro), el zócalo J2 del módulo I2C, la botonera B1–B4 y J1 hacia la tarjeta de control.*

*Esquemático por bloques (KiCad 9, hoja A4): A conector a la tarjeta de control, B pantalla y módulo I2C, C botonera, D montaje.*

---

## 0. Mapa del panel

| # | Bloque | Componentes | En una frase |
| --- | --- | --- | --- |
| 1 | [Conector a la tarjeta de control](#1-conector-a-la-tarjeta-de-control-j1--j7) | J1, C1 | Un cable 1:1 de 5 hilos: I2C, 5 V, GND y botonera |
| 2 | [Pantalla y módulo I2C](#2-pantalla-lcd-y-módulo-i2c-j2) | J2, C2 | El módulo PCF8574 entra **directo** al zócalo, sin cables |
| 3 | [Botonera](#3-botonera-4-botones-en-un-solo-pin) | SW1–SW4, R1–R4, C3 | 4 botones en un solo pin analógico (A7 del AUX) |
| 4 | [Montaje mecánico](#4-montaje-mecánico-162-o-204) | H1–H11 | La misma placa sirve para LCD 16×2 o 20×4 |
| 5 | [Qué muestra y qué configura](#5-qué-muestra-y-qué-configura-propuesta-de-firmware) | Firmware del AUX | Pantallas de datos y menú SETUP |

---

## 1. Conector a la tarjeta de control (J1 ↔ J7)

| J1 | Señal | Va a (tarjeta de control) | Notas |
| --- | --- | --- | --- |
| 1 | SCL_LCD | D5 del AUX | I2C por software, **en un bus aparte** del enlace CRÍTICO–AUX: si la pantalla se cuelga, no tumba el enlace |
| 2 | SDA_LCD | D4 del AUX | — |
| 3 | 5V | Riel de 5 V (7805) | Pantalla, luz de fondo y botonera |
| 4 | GND | GND | Retorno común |
| 5 | BOTON_LCD | A7 del AUX, con **R42 = 10 kΩ a 5 V** | El pull-up está **en la tarjeta de control**, no aquí |

| Ref. | Valor | Qué hace | Por qué |
| --- | --- | --- | --- |
| **J1** | Tira macho 1×5, 2.54 mm, **a 90°** | Sale por el canto derecho | Vertical, con el conector del cable puesto, mediría ~22 mm y chocaría con el frente |
| **C1** | 10 µF electrolítico (5 mm) | Reserva a la entrada del cable | La luz de fondo pide corriente en picos; el cable tiene resistencia e inductancia |

- **Cable:** 5 hilos, **pin n con pin n** (1:1). Trenza BOTON_LCD con GND. Largo recomendado: menos de 50 cm.
- **Si el cable se suelta:** A7 queda en 5 V por R42 = "ningún botón". La pantalla se apaga y **el inversor no cambia de estado**.

---

## 2. Pantalla LCD y módulo I2C (J2)

La pantalla usa el módulo adaptador **PCF8574** (FC-113 o equivalente) soldado atrás del LCD. Sus 4 pines salen **rectos, perpendiculares al módulo**, apuntando hacia esta placa. Por eso entran **directo en el zócalo J2**: el LCD se monta en sus postes y queda conectado, sin cables.

| J2 | Señal | Pin del módulo PCF8574 |
| --- | --- | --- |
| 1 (cuadrado) | GND | GND |
| 2 | 5V | VCC |
| 3 | SDA_LCD | SDA |
| 4 | SCL_LCD | SCL |

| Ref. | Valor | Qué hace | Por qué |
| --- | --- | --- | --- |
| **J2** | Tira **hembra** 1×4, 2.54 mm, vertical (8.5 mm) | Recibe los pines del módulo I2C | Desmontable: la pantalla se cambia sin soldar |
| **C2** | 100 nF cerámico | Desacople pegado al zócalo | Filtra el ruido de alta frecuencia del PCF8574. **Bajo (≤ 5 mm):** queda debajo del módulo |

- **Orden de pines:** casi todos los módulos traen GND · VCC · SDA · SCL. **Revisa la serigrafía del tuyo** antes de montarlo: si viene en otro orden, el 5 V queda al revés.
- **Dirección I2C:** típica **0x27** (PCF8574T) o **0x3F** (PCF8574AT). El firmware la busca sola al arrancar (ver la sección 5).
- **Contraste:** potenciómetro azul del módulo. Si la pantalla prende pero no muestra nada, casi siempre es el contraste.
- **Luz de fondo:** el puente (jumper) del módulo la habilita. El firmware la puede apagar después de un rato sin tocar botones.
- **Pull-ups del I2C:** la mayoría de los módulos traen sus resistencias de pull-up en SDA y SCL. Si el tuyo no las trae, agrega 4.7 kΩ a 5 V en cada línea.

---

## 3. Botonera: 4 botones en un solo pin

Cada botón conecta BOTON_LCD a GND **con su propia resistencia, en paralelo** (no en cadena: si una falla, solo falla ese botón). Con R42 = 10 kΩ en la tarjeta de control se forma un divisor: **V = 5 V × Rb / (10 kΩ + Rb)**.

| Botón | Resistencia (E24) | Voltaje en A7 | Cuentas ADC | Función propuesta |
| --- | --- | --- | --- | --- |
| Ninguno | — | 5.00 V | 1023 | — |
| **B1** | R1 = **2.4 kΩ** | 0.97 V | ~198 | **ATRÁS / ESC** |
| **B2** | R2 = **6.8 kΩ** | 2.02 V | ~414 | **ARRIBA / −** |
| **B3** | R3 = **15 kΩ** | 3.00 V | ~614 | **ABAJO / +** |
| **B4** | R4 = **39 kΩ** | 3.98 V | ~815 | **OK / ENTRAR** (sostenido 3 s: SETUP) |

| Ref. | Valor | Qué hace | Por qué |
| --- | --- | --- | --- |
| **SW1–SW4** | Botón táctil THT 6 × 6 mm | Cierra BOTON_LCD a GND por su resistencia | La huella es la misma para cualquier altura de actuador: se elige según el frente (sección 4) |
| **R1–R4** | 2.4 k / 6.8 k / 15 k / 39 k, ¼ W, 1 % de preferencia | Fijan el voltaje de cada botón | Separación de ~1 V entre botones: tolera resistencias de 5 % y ruido sin confundir un botón con otro. Corriente máxima: 0.4 mA |
| **C3** | 100 nF, **opcional (DNP)** | Filtro de la línea | Solo si el cable es largo o hay ruido. De entrada no se coloca |

- **Firmware:** umbrales en 0.5 / 1.5 / 2.5 / 3.5 / 4.5 V (~102 / 307 / 512 / 716 / 921 cuentas). Antirrebote: 3 o 4 lecturas iguales (~30 ms). Con dos botones oprimidos a la vez se lee el de menor número.
- **No cambies R42** en la tarjeta de control: todos los voltajes dependen de ella.
- **Prueba con multímetro** (panel conectado, sin pantalla): mide BOTON_LCD contra GND y oprime cada botón; debe dar la columna "Voltaje en A7" con ±0.1 V.

---

## 4. Montaje mecánico: 16×2 o 20×4

La misma placa acepta **las dos pantallas**. Ambas se alinean por el **pin 1 de su conector de 16 pines**. Como el módulo I2C va soldado en ese conector, sus pines caen **en el mismo lugar** con cualquiera de las dos, y J2 sirve para ambas.

| Ref. | Para | Medida | Notas |
| --- | --- | --- | --- |
| **H1** | LCD 16×2 **y** 20×4 | Ranura M3 de 7.2 × 3.2 mm | Esquina superior izquierda: los barrenos de las dos pantallas se enciman y comparten la ranura |
| **H2–H4** | LCD 16×2 (80 × 36 mm) | Ranuras M3 de 5.2 × 3.2 mm, a 75 × 31 mm entre centros | — |
| **H5–H7** | LCD 20×4 (98 × 60 mm) | Ranuras M3 de 5.2 × 3.2 mm, a 93 × 55 mm entre centros | — |
| **H8–H11** | Fijación al gabinete | Barrenos M3 en las esquinas | — |

- **Ranuras de ±1 mm:** absorben la diferencia entre marcas de pantalla. Las ranuras son huellas propias, en la librería `Isla_del_Sol.pretty` que viene con el proyecto (`fp-lib-table`).
- **Pila de alturas:** los postes del LCD fijan a qué altura quedan los pines I2C. Para que entren unos 3 mm en el zócalo de 8.5 mm:

  **Altura del poste ≈ (cara trasera del LCD a la punta de los pines I2C) + 5.5 mm**

  Con los módulos comunes salen postes de **15 a 18 mm**.
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
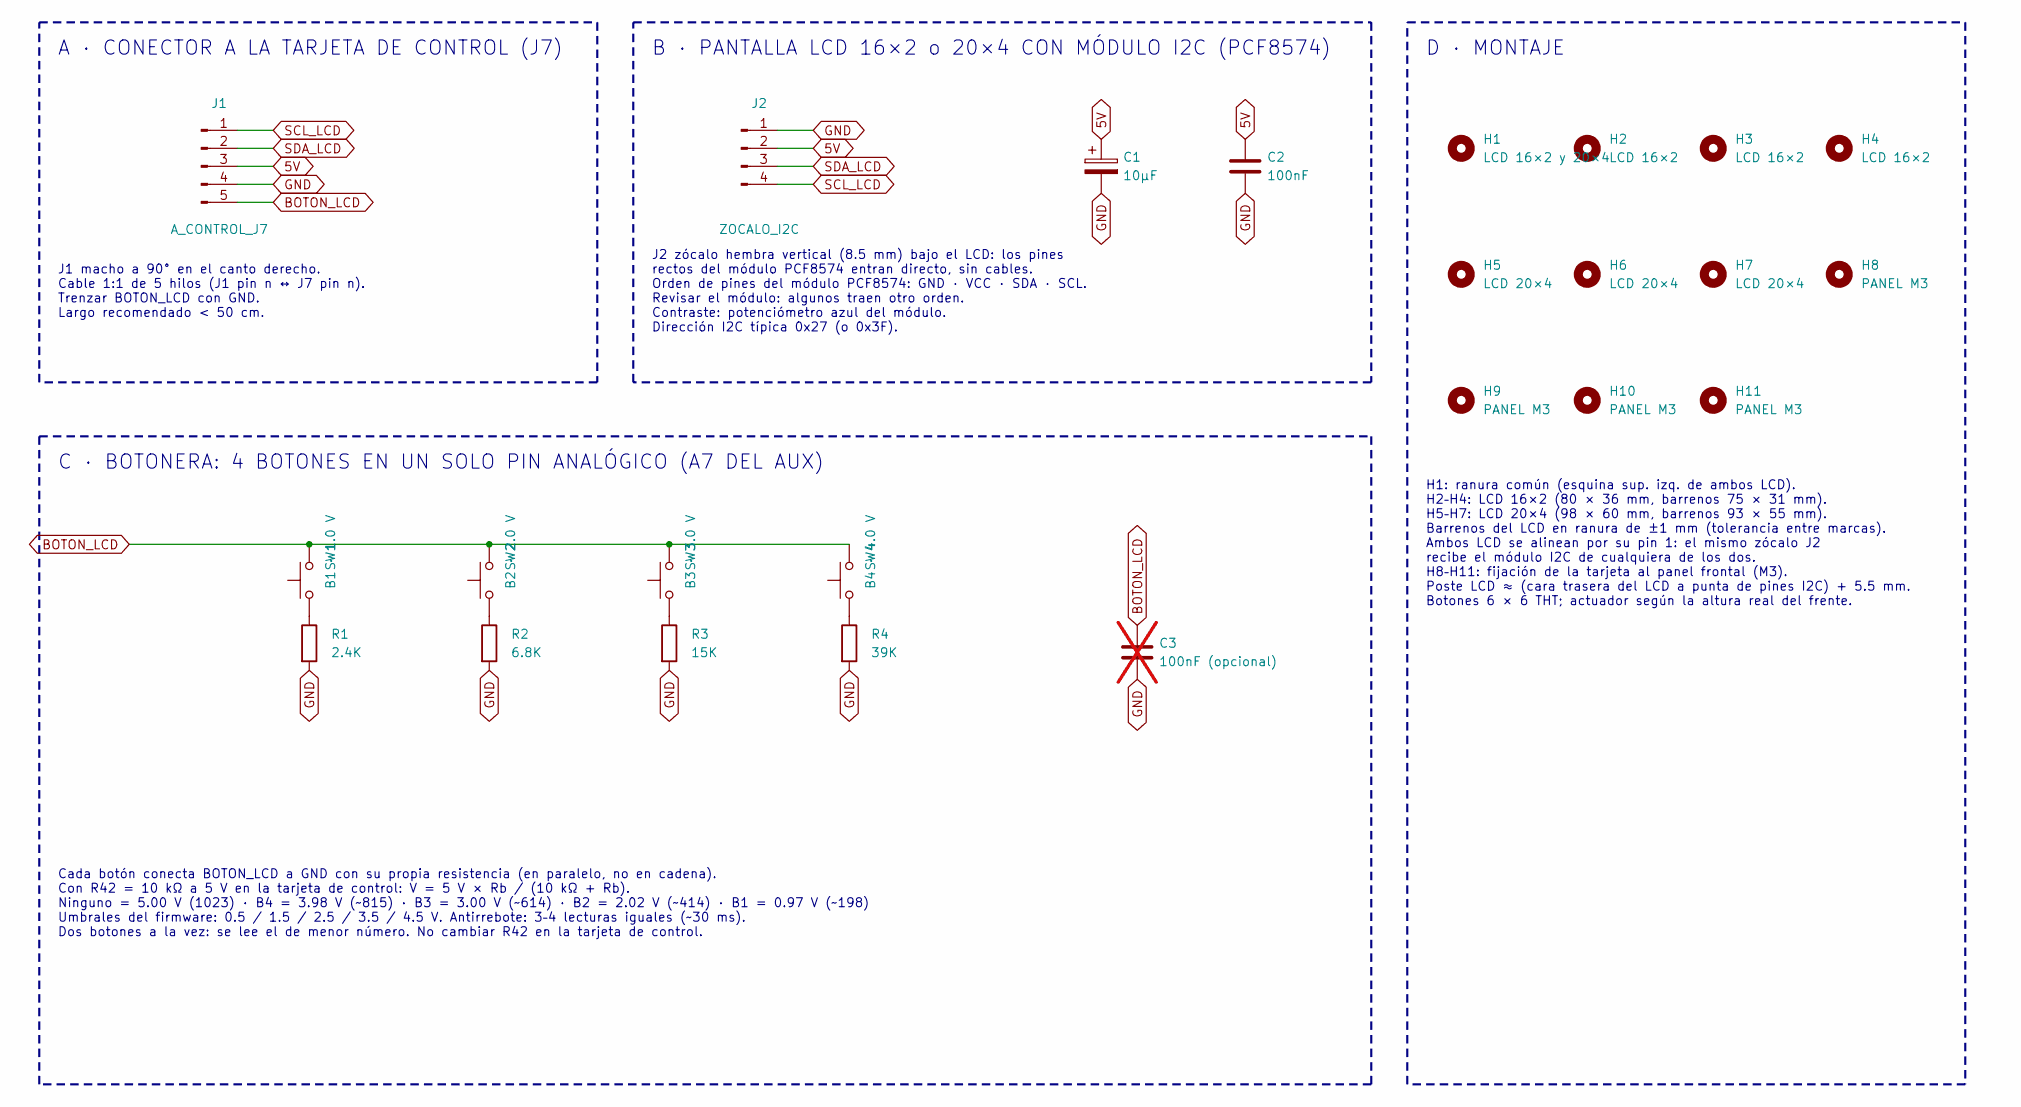
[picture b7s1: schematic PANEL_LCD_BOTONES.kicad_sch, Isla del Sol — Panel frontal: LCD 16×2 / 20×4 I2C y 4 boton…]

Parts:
C1: 10µF; CP_Radial_D5.0mm_P2.00mm
C2: 100nF; C_Disc_D3.0mm_W2.0mm_P2.50mm
C3: 100nF (opcional); C_Disc_D3.0mm_W2.0mm_P2.50mm; not fitted
H1: LCD 16×2 y 20×4; Ranura_M3_7.2x3.2
H2, H3, H4: LCD 16×2; Ranura_M3_5.2x3.2
H5, H6, H7: LCD 20×4; Ranura_M3_5.2x3.2
H8, H9, H10, H11: PANEL M3; MountingHole_3.2mm_M3
J1: A_CONTROL_J7; PinHeader_1x05_P2.54mm_Horizontal
J2: ZOCALO_I2C; PinSocket_1x04_P2.54mm_Vertical
R1: 2.4K; R_Axial_DIN0204_L3.6mm_D1.6mm_P5.08mm_Horizontal
R2: 6.8K; R_Axial_DIN0204_L3.6mm_D1.6mm_P5.08mm_Horizontal
R3: 15K; R_Axial_DIN0204_L3.6mm_D1.6mm_P5.08mm_Horizontal
R4: 39K; R_Axial_DIN0204_L3.6mm_D1.6mm_P5.08mm_Horizontal
SW1: B1 · 1.0 V; SW_PUSH_6mm_H13mm
SW2: B2 · 2.0 V; SW_PUSH_6mm_H13mm
SW3: B3 · 3.0 V; SW_PUSH_6mm_H13mm
SW4: B4 · 4.0 V; SW_PUSH_6mm_H13mm

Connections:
5V: C1.1, C2.1, J1.3, J2.2
BOTON_LCD: C3.1, J1.5, SW1.2, SW2.2, SW3.2, SW4.2
GND: C1.2, C2.2, C3.2, J1.4, J2.1, R1.2, R2.2, R3.2, R4.2
unnamed: R1.1, SW1.1
unnamed: R2.1, SW2.1
unnamed: R3.1, SW3.1
unnamed: R4.1, SW4.1
SCL_LCD: J1.1, J2.4
SDA_LCD: J1.2, J2.3

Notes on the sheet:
A · CONECTOR A LA TARJETA DE CONTROL (J7)
J1 macho a 90° en el canto derecho. Cable 1:1 de 5 hilos (J1 pin n ↔ J7 pin n). Trenzar BOTON_LCD con GND. Largo recomendado < 50 cm.
B · PANTALLA LCD 16×2 o 20×4 CON MÓDULO I2C (PCF8574)
J2 zócalo hembra vertical (8.5 mm) bajo el LCD: los pines rectos del módulo PCF8574 entran directo, sin cables. Orden de pines del módulo PCF8574: GND · VCC · SDA · SCL. Revisar el módulo: algunos traen otro orden. Contraste: potenciómetro azul del módulo. Dirección I2C típica 0x27 (o 0x3F).
C · BOTONERA: 4 BOTONES EN UN SOLO PIN ANALÓGICO (A7 DEL AUX)
Cada botón conecta BOTON_LCD a GND con su propia resistencia (en paralelo, no en cadena). Con R42 = 10 kΩ a 5 V en la tarjeta de control: V = 5 V × Rb / (10 kΩ + Rb). Ninguno = 5.00 V (1023) · B4 = 3.98 V (~815) · B3 = 3.00 V (~614) · B2 = 2.02 V (~414) · B1 = 0.97 V (~198) Umbrales del firmware: 0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
D · MONTAJE
H1: ranura común (esquina sup. izq. de ambos LCD). H2–H4: LCD 16×2 (80 × 36 mm, barrenos 75 × 31 mm). H5–H7: LCD 20×4 (98 × 60 mm, barrenos 93 × 55 mm). Barrenos del LCD en ranura de ±1 mm (tolerancia entre marcas). Ambos LCD se alinean por su pin 1: el mismo zócalo J2 recibe el módulo I2C de cualq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
